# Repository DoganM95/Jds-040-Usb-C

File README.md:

# DS4-UsbC-Mod

Custom pcb to replace Dualshock 4's micro b port with usb c (PD compatible). It was made to replace the jds-040 model but might be a compatible replacement for other models.

<table>
  <tr>
    <td></td>
    <td></td>
  </tr>
</table>

<table>
  <tr>
    <td></td>
    <td></td>
  </tr>
</table>

## FPC pinout

Starting with the pin that is closest to the charge port and ending with the pin that is closest to the led's:

1. GND
2. GND
3. D +
4. D -
5. GND
6. GND
7. Green LED (3V3_G)
8. Red LED VCC (2V2_G)
9. Blue LED VCC (3V_G)
10. LED VCC
11. USB 5V
12. USB 5V

## Key features
- Usb C port (with D+ and D-)
- Compatible with power delivery (communicates to get 5V)
- Compatible with any 5V usb port
- Uses easily accessible components (Aliexpress)
- Dual RGB led's

## Parts
- PCB: Get the latest gerber zip in releases and order it from Jlcpcb, with 1mm PCB thickness
- FPC connector (pins:12, pitch:0.5mm. Salvage it from an existing board -> ) https://a.aliexpress.com/_EjykXX1
- Led's (RGB, side view) https://a.aliexpress.com/_EHr7vQn
- Resistors (size:0603, res:5.1kOhm) https://a.aliexpress.com/_EIPYwrH
- USB C (female, pins:16, padding-bottom:0.8mm) https://a.aliexpress.com/_EJhQRSJ

## Tools (recommended next to the obvious)
- Hot plate
- Flux
- Solder wick
- Hot air gun

# Procedure
- Get the salvageable micro b module from aliexpress ready
- Use a hot air gun to desolder the usb micro b port
- Fire up the hot plate & put the pcb on it
- Steal the fpc connector from it
- Get the blank usb c pcb ready
- Solder the fpc connector to it (sides first in good position)
- Solder the usb c port's 4 shell pads in good position
- Solder usb c pins
- Solder solder smd resistors
- Solder smd led's
  - Put solder on the pcb pads
  - Put solder on the led's pads
  - Solder the middle 2 pins first
  - Solder the sides

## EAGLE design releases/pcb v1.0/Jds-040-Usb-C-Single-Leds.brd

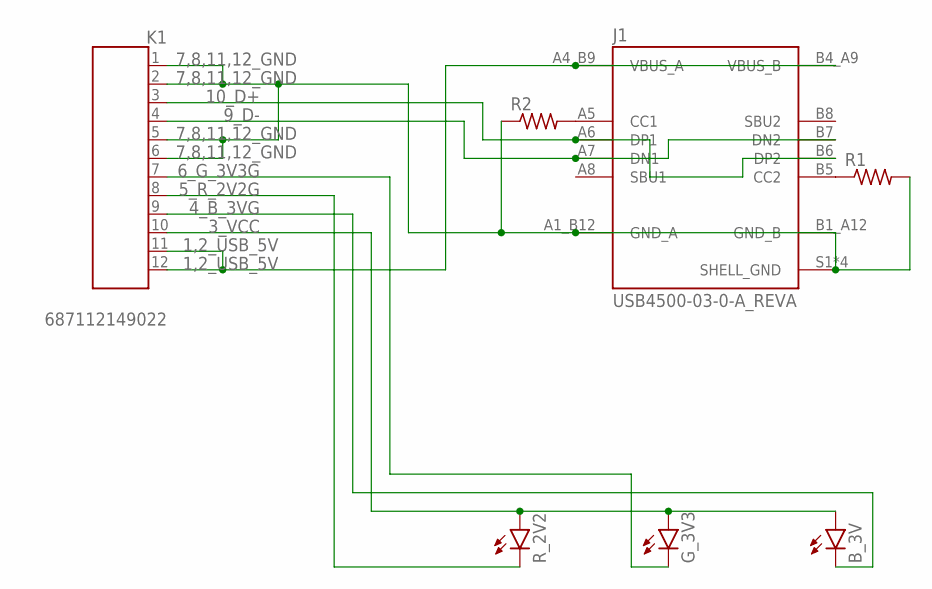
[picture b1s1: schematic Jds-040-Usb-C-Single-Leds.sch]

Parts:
B_3V: BEAGLEBONE_BLUE_LED0603; BEAGLEBONE_BLUE_BEAGLEBONE_BLUE_LED-0603
G_3V3: BEAGLEBONE_BLUE_LED0603; BEAGLEBONE_BLUE_BEAGLEBONE_BLUE_LED-0603
J1: USB4500-03-0-A_REVA; GCT_USB4500-03-0-A_REVA
K1: 687112149022
R1, R2: 5k1; RES_0603
R_2V2: BEAGLEBONE_BLUE_LED0603; BEAGLEBONE_BLUE_BEAGLEBONE_BLUE_LED-0603

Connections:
1,2_USB_5V: J1.A4_B9 (VBUS_A), J1.B4_A9 (VBUS_B), K1.11, K1.12
3_VCC: B_3V.A, G_3V3.A, K1.10, R_2V2.A
4_B_3VG: B_3V.C, K1.9
5_R_2V2G: K1.8, R_2V2.C
6_G_3V3G: G_3V3.C, K1.7
7,8,11,12_GND: J1.A1_B12 (GND_A), J1.B1_A12 (GND_B), J1.S1 (SHELL_GND), J1.S2 (SHELL_GND), J1.S3 (SHELL_GND), J1.S4 (SHELL_GND), K1.1, K1.2, K1.5, K1.6, R1.2, R2.1
9_D-: J1.A7 (DN1), J1.B7 (DN2), K1.4
10_D+: J1.A6 (DP1), J1.B6 (DP2), K1.3
unnamed: J1.B5 (CC2), R1.1
unnamed: J1.A5 (CC1), R2.2

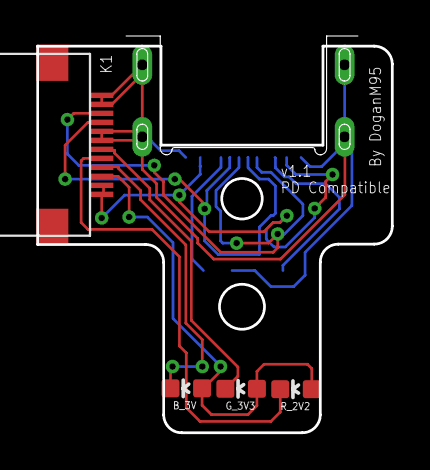
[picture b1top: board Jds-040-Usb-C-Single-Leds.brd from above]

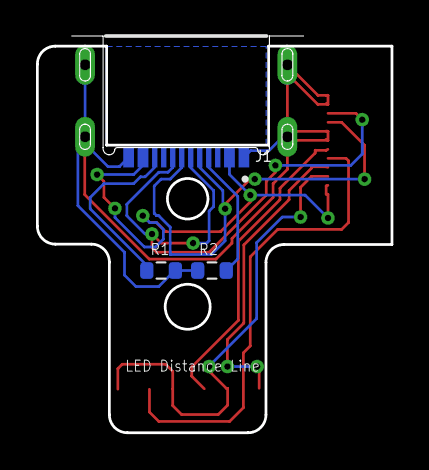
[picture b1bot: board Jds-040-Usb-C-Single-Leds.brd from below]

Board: 2 copper layers, 19.7 x 22.0 mm, 7 parts (3 on the bottom side), 10 nets.

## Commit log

2023-08-02 move images
2023-08-02 add v1.1 gerber files
2023-08-02 rename zip for release
2023-08-02 fix images
2023-08-20 add v1.1 pcb gerber
2023-08-30 add gbr files for v1.0
2023-08-30 add gbr files for v1.1
2023-11-10 ignore stuff
2023-11-10 ignore CAM
2023-11-10 restructure & open source
2023-11-10 add license

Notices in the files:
parts and their libraries:
FPC_Connectors_Flat_Flexible_Cable_rev15: Copyright: Würth Elektronik
